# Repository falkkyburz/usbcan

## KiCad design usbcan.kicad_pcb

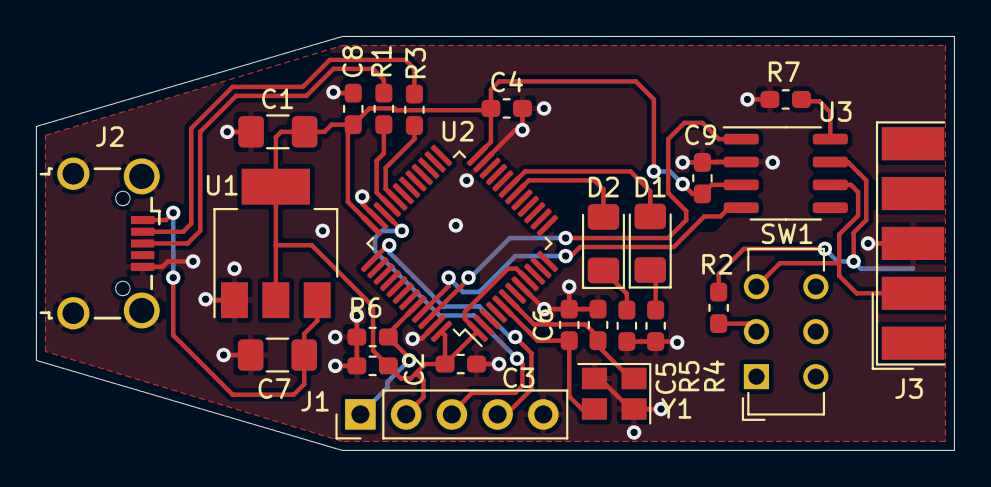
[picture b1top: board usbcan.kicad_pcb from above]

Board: 2 copper layers, 51.0 x 23.0 mm, 26 parts (0 on the bottom side), 22 nets.

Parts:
C1, C7: 10u; C_1206_3216Metric_Pad1.42x1.75mm_HandSolder
C2, C3, C4, C8, C9: 100n; C_0603_1608Metric_Pad1.05x0.95mm_HandSolder
C5, C6: 18p; C_0603_1608Metric_Pad1.05x0.95mm_HandSolder
D1, D2: LED; LED_1206_3216Metric_Pad1.42x1.75mm_HandSolder
J1: Conn_01x05; PinHeader_1x05_P2.54mm_Vertical
J2: USB_B_Micro; USB_Micro-B_Wuerth_629105150521_CircularHoles
J3: DB9_Male; DSUB-9_Male_EdgeMount_P2.77mm
R1, R3: 33; R_0603_1608Metric_Pad1.05x0.95mm_HandSolder
R2, R4, R5: 120; R_0603_1608Metric_Pad1.05x0.95mm_HandSolder
R6, R7: 10k; R_0603_1608Metric_Pad1.05x0.95mm_HandSolder
SW1: SW_SPDT; SW_CuK_JS202011CQN_DPDT_Straight
U1: AP1117-33; SOT-223-3_TabPin2
U2: STM32F042C6Tx; LQFP-48_7x7mm_P0.5mm
U3: MCP2551-I-SN; SOIC-8_3.9x4.9mm_P1.27mm
Y1: Crystal_GND24; Crystal_SMD_3225-4Pin_3.2x2.5mm

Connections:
+3V3: C1.1, C2.1, C3.1, C4.1, C8.1, C9.1, J1.2, U1.2, U2.1, U2.9, U2.24, U2.36, U2.48, U3.3
+5V: C7.1, J2.1, U1.3
/BOOT: J1.1, R6.1, U2.44
/CANH: J3.7, R2.1, U3.7
/CANL: J3.2, SW1.3, U3.6
/CANL1: R2.2, SW1.2
/LEDK_G: D2.1, R5.1
/LEDK_R: D1.1, R4.1
/LED_G: D2.2, U2.18
/LED_R: D1.2, U2.19
/RS: R7.1, U3.8
/RXD: U2.45, U3.4
/SWCLK: J1.4, U2.37
/SWDIO: J1.3, U2.34
/TXD: U2.46, U3.1
/USBN: J2.2, R3.2
/USBN1: R3.1, U2.32
/USBP: J2.3, R1.2
/USBP1: R1.1, U2.33
/XTAL1: C6.1, U2.5, Y1.3
/XTAL2: C5.2, U2.6, Y1.1
GND: C1.2, C2.2, C3.2, C4.2, C5.1, C6.2, C7.2, C8.2, C9.2, J1.5, J2.5, J2.6, J3.3, J3.6, R4.2, R5.2, R6.2, R7.2, U1.1, U2.8, U2.23, U2.35, U2.47, U3.2, Y1.2, Y1.4

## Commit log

2021-06-16 Initial commit.
